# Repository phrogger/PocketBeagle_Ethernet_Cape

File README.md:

# PocketBeagle_Ethernet_Cape
Design Files for an Ethernet Cape for the PocketBeagle.

This design and documentation are released under the TAPR Open Hardware License.
https://www.tapr.org/ohl.html
There is no warranty as to suitability or applicability for any purpose.
There may be additional licenses or restrictions associated with the use of the Microchip LAN9500A device.

## Notes:
Board Files are Eagle 7.7

The PocketBeagle is configured so that USB Port 0 is a "slave port" only, and is the port pinned out to the Micro-USB connector on the PocketBeagle.

USB Port 1 is configured as a Master, only. It is pinned out to the I/O Expansion Connector P1, pins 3, 5, 7, 9, 11, 13, and 15. This is the port used by this Ethernet 'Cape'.

This design uses a QFN package and surface mount parts as small as 0402, in order to fit the Ethernet interface in a space as small as the PocketBeagle footprint. It is not an appropriate project for someone not experienced in SMT assembly.

The PocketBeagle has a totally symmetrical IO connector configuration. There is nothing that prevents the reversed or offset insertion of this cape. Components may be damaged if the cape is installed backwards, or offset.

This design includes an EEPROM for the permanent assignment of a MAC address to the Ethernet interface. There are software tools for the programming of this EEPROM device in the LAN9500A section of the Microchip website.
Obtaining a legitimate MAC address for use in any assembled boards is the responsibility of the builder.

Bare PC boards built from this Eagle ".brd" file are available from OshPark, minimum order of three boards:
https://oshpark.com/shared_projects/GOEnFXdS

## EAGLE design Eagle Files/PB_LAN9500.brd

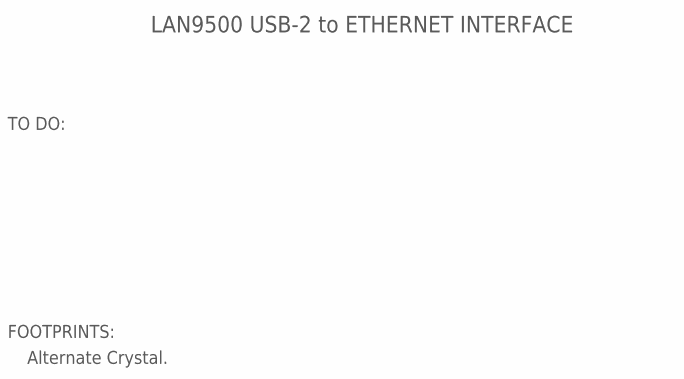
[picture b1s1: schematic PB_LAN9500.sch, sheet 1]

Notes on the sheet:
LAN9500 USB-2 to ETHERNET INTERFACE
TO DO:
FOOTPRINTS:
Alternate Crystal.

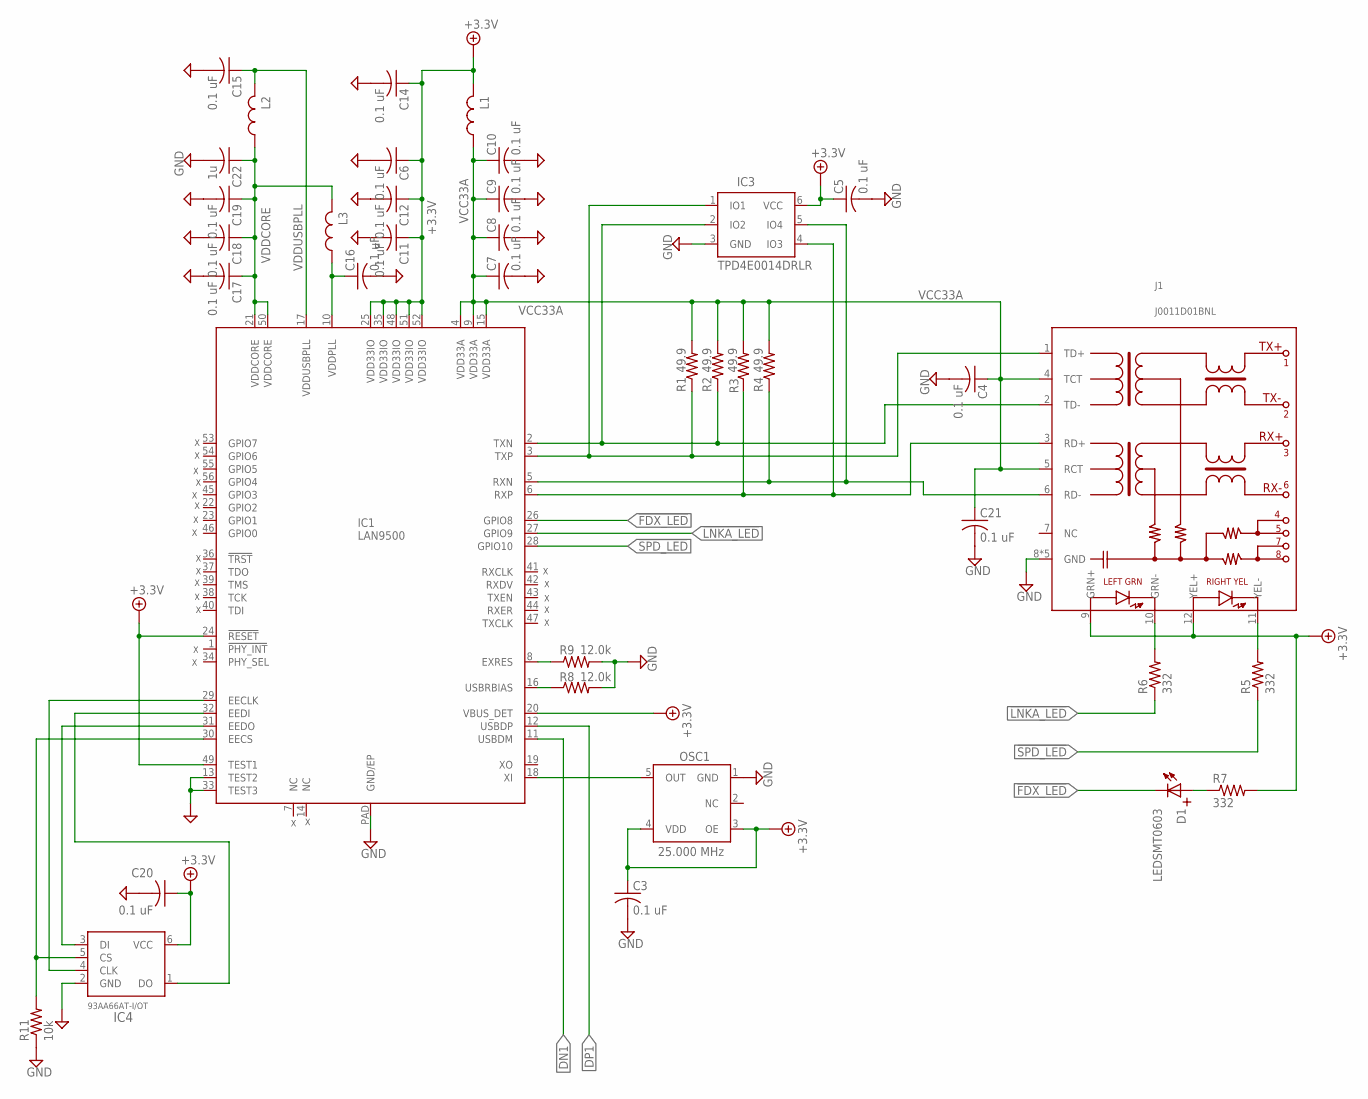
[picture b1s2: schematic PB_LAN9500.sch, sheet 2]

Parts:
C3, C4, C5, C6, C7, C8, C9, C10, C11, C12, C14, C15, C16, C17, C18, C19, C20, C21: 0.1 uF; C0402
C22: 1u; C0805
D1: LEDSMT0603; LED0603
IC1: LAN9500; QFN56
IC3: TPD4E0014DRLR; SOT-553-6
IC4: 93AA66AT-I/OT; SOT23-6
J1: J0011D01BNL
L1, L2, L3: L0603AS
OSC1: 25.000 MHz; SOT23-5
R1, R2, R3, R4: 49.9; R0603
R5, R6, R7: 332; R0603
R8, R9: 12.0k; R0603
R11: 10k; R0603

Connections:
!FDX_LED: D1.P$2 (K), IC1.26 (GPIO8)
!LNKA_LED: IC1.27 (GPIO9), R6.1
!SPD_LED: IC1.28 (GPIO10), R5.1
+3.3V: C3.1, C5.1, C6.1, C11.1, C12.1, C14.1, C20.1, IC1.20 (VBUS_DET), IC1.24 (!RESET), IC1.25 (VDD33IO), IC1.35 (VDD33IO), IC1.48 (VDD33IO), IC1.49 (TEST1), IC1.51 (VDD33IO), IC1.52 (VDD33IO), IC3.6 (VCC), IC4.6 (VCC), J1.9 (GRN+), J1.12 (YEL+), L1.2, OSC1.3 (OE), OSC1.4 (VDD), R7.2; also elsewhere on the board
DN1: IC1.11 (USBDM); also elsewhere on the board
DP1: IC1.12 (USBDP); also elsewhere on the board
GND: C3.2, C4.2, C5.2, C6.2, C7.2, C8.2, C9.2, C10.2, C11.2, C12.2, C14.2, C15.2, C16.2, C17.2, C18.2, C19.2, C20.2, C21.2, C22.2, IC1.13 (TEST2), IC1.33 (TEST3), IC1.PAD (GND/EP), IC3.3 (GND), IC4.2 (GND), J1.8 (GND), J1.GND1 (GND), J1.GND2 (GND), J1.GND3 (GND), J1.GND4 (GND), OSC1.1 (GND), R8.2, R9.2, R11.1; also elsewhere on the board
unnamed: J1.11 (YEL-), R5.2
unnamed: IC1.30 (EECS), IC4.5 (CS), R11.2
unnamed: IC1.29 (EECLK), IC4.4 (CLK)
unnamed: IC1.31 (EEDO), IC4.3 (DI)
unnamed: IC1.32 (EEDI), IC4.1 (DO)
unnamed: IC1.8 (EXRES), R9.1
unnamed: IC1.16 (USBRBIAS), R8.1
unnamed: D1.P$1 (A), R7.1
unnamed: J1.10 (GRN-), R6.2
unnamed: IC1.18 (XI), OSC1.5 (OUT)
RXN: IC1.5 (RXN), IC3.5 (IO4), J1.6 (RD-), R4.1
RXP: IC1.6 (RXP), IC3.4 (IO3), J1.3 (RD+), R3.1
TXN: IC1.2 (TXN), IC3.2 (IO2), J1.2 (TD-), R2.1
TXP: IC1.3 (TXP), IC3.1 (IO1), J1.1 (TD+), R1.1
VCC33A: C4.1, C7.1, C8.1, C9.1, C10.1, C21.1, IC1.4 (VDD33A), IC1.9 (VDD33A), IC1.15 (VDD33A), J1.4 (TCT), J1.5 (RCT), L1.1, R1.2, R2.2, R3.2, R4.2
VDDCORE: C17.1, C18.1, C19.1, C22.1, IC1.21 (VDDCORE), IC1.50 (VDDCORE), L2.1, L3.2
VDDPLL: C16.1, IC1.10 (VDDPLL), L3.1
VDDUSBPLL: C15.1, IC1.17 (VDDUSBPLL), L2.2

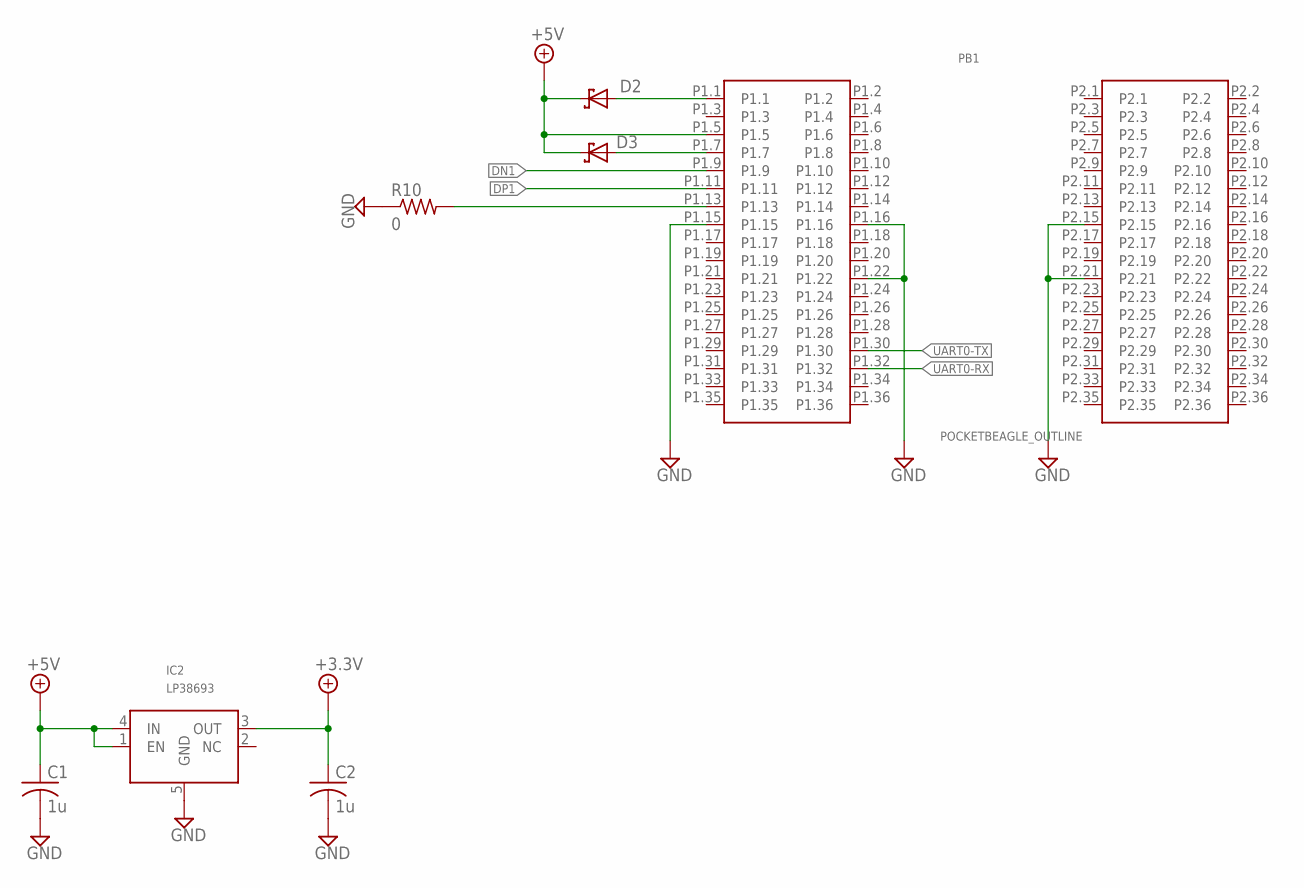
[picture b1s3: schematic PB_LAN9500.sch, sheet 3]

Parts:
C1, C2: 1u; C0805
D2, D3: MBRAF1540; SMA-FL
IC2: LP38693; SOT-223-4
PB1: POCKETBEAGLE_OUTLINE; PB_OUTLINE
R10: 0; R0603

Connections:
+3.3V: C2.1, IC2.3 (OUT); also elsewhere on the board
+5V: C1.1, D2.C, D3.C, IC2.1 (EN), IC2.4 (IN), PB1.P1.5
DN1: PB1.P1.9; also elsewhere on the board
DP1: PB1.P1.11; also elsewhere on the board
GND: C1.2, C2.2, IC2.5 (GND), PB1.P1.15, PB1.P1.16, PB1.P1.22, PB1.P2.15, PB1.P2.21, R10.1; also elsewhere on the board
ID1: PB1.P1.13, R10.2
unnamed: D3.A, PB1.P1.7
unnamed: D2.A, PB1.P1.1
UART0-RX: PB1.P1.32
UART0-TX: PB1.P1.30

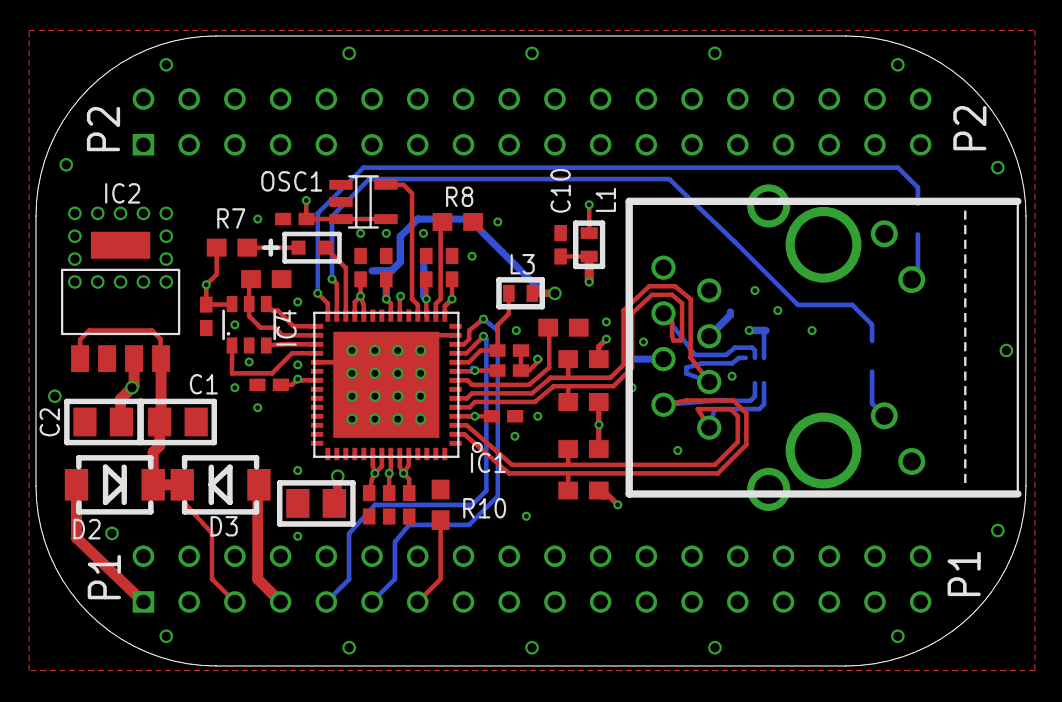
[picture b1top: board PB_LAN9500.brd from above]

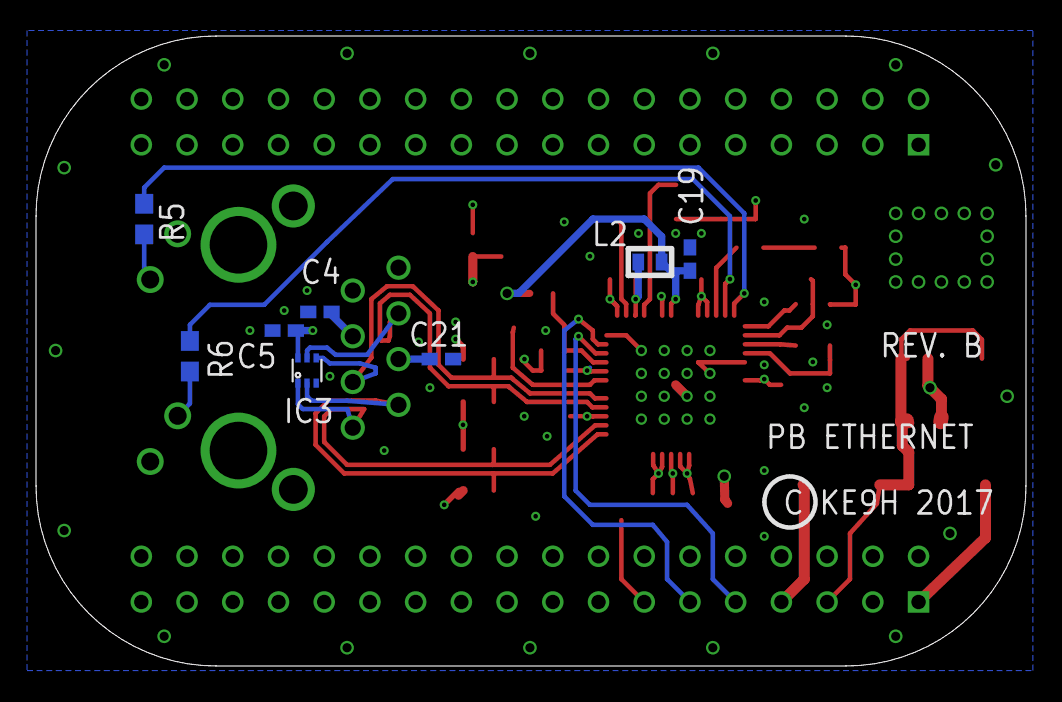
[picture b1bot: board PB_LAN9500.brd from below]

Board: 4 copper layers, 55.0 x 35.0 mm, 45 parts (8 on the bottom side), 29 nets.

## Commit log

2019-08-03 Initial Commit of Eagle Design Files
2019-08-04 Added ".jpg" of assembled unit.
